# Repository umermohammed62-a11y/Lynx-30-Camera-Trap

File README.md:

Lynx-30: Simulation-Driven Low-Power Long-Range Camera Trap System

Overview

Lynx-30 is a low-power wireless camera trap system designed around the ESP32-CAM module. The system combines motion detection, infrared illumination, and efficient power management to provide battery-powered image capture for wildlife monitoring and remote sensing applications.

The project was developed using a modular hierarchical design approach and includes complete schematic capture, PCB layout, BOM generation, and manufacturing-ready Gerber files.

Features

* Low-power battery-powered operation
* ESP32-CAM image capture and wireless connectivity
* PIR-based motion detection
* Infrared illumination for night operation
* High-efficiency TPS63060 power architecture
* 5V and 3.3V regulated power rails
* PMOS-based power gating for IR LEDs
* Hierarchical schematic design
* Manufacturing-ready PCB design
* Support for 2-layer and 4-layer PCB stackups

System Architecture

Battery
   ↓
TPS63060 Buck-Boost Converter
   ↓
V_SYS_5V
   ├── ESP32-CAM
   ├── IR Illumination
   └── LDO Regulator
           ↓
        V_SYS_3V3
           ├── PIR Sensor
           └── Control Logic

Hardware Components

Main Controller

* ESP32-CAM AI Thinker Module

Power Management

* TPS63060 Buck-Boost Converter
* 3.3V LDO Regulator

Motion Detection

* PIR Sensor Module

Illumination

* IR LEDs
* PMOS High-Side Switching Circuit

Interfaces

* UART Programming Header
* MicroSD Storage

Power Architecture

The system uses a TPS63060 high-efficiency buck-boost converter to generate a regulated 5V rail from battery input.

The 5V rail supplies:

* ESP32-CAM
* IR illumination circuit

A secondary LDO regulator generates a 3.3V rail for:

* PIR sensor
* Control logic
* MOSFET gate drive circuitry

PCB Stackup

2-Layer Version

* Top Layer: Components and signal routing
* Bottom Layer: Ground plane

4-Layer Version

* Layer 1: Signal routing
* Layer 2: Ground plane
* Layer 3: Power plane
* Layer 4: Signal routing

Design Tools

* KiCad

Project Structure

Lynx-30-Camera-Trap
│
├── Documentation
│   ├── Project_Report.pdf
│   ├── System_Architecture.pdf
│   └── Design_Notes.pdf
│
├── KiCad
│   ├── Schematics
│   ├── PCB
│   └── Libraries
│
├── Gerbers
│
├── BOM
│   └── BOM.csv
│
├── Images
│   ├── PCB_Top.png
│   ├── PCB_Bottom.png
│   ├── PCB_3D.png
│   └── System_Block_Diagram.png
│
└── README.md
```
Deliverables

* Complete hierarchical schematic
* PCB layout
* BOM (Bill of Materials)
* Gerber files
* Pick-and-place files
* PCB 3D render images
* Engineering documentation

Future Improvements

* Deep sleep optimization
* Solar charging capability
* Machine learning-based object detection
* Cloud connectivity
* LoRa communication support
* Environmental sensors integration

Applications

* Wildlife monitoring
* Security surveillance
* Remote sensing
* Smart agriculture
* IoT edge devices

Author

Engr Umer Mohammed**

Electrical and Computer Engineer

Specialization: Power Engineering

Designed using professional PCB design practices with a focus on low-power embedded systems and manufacturable hardware.

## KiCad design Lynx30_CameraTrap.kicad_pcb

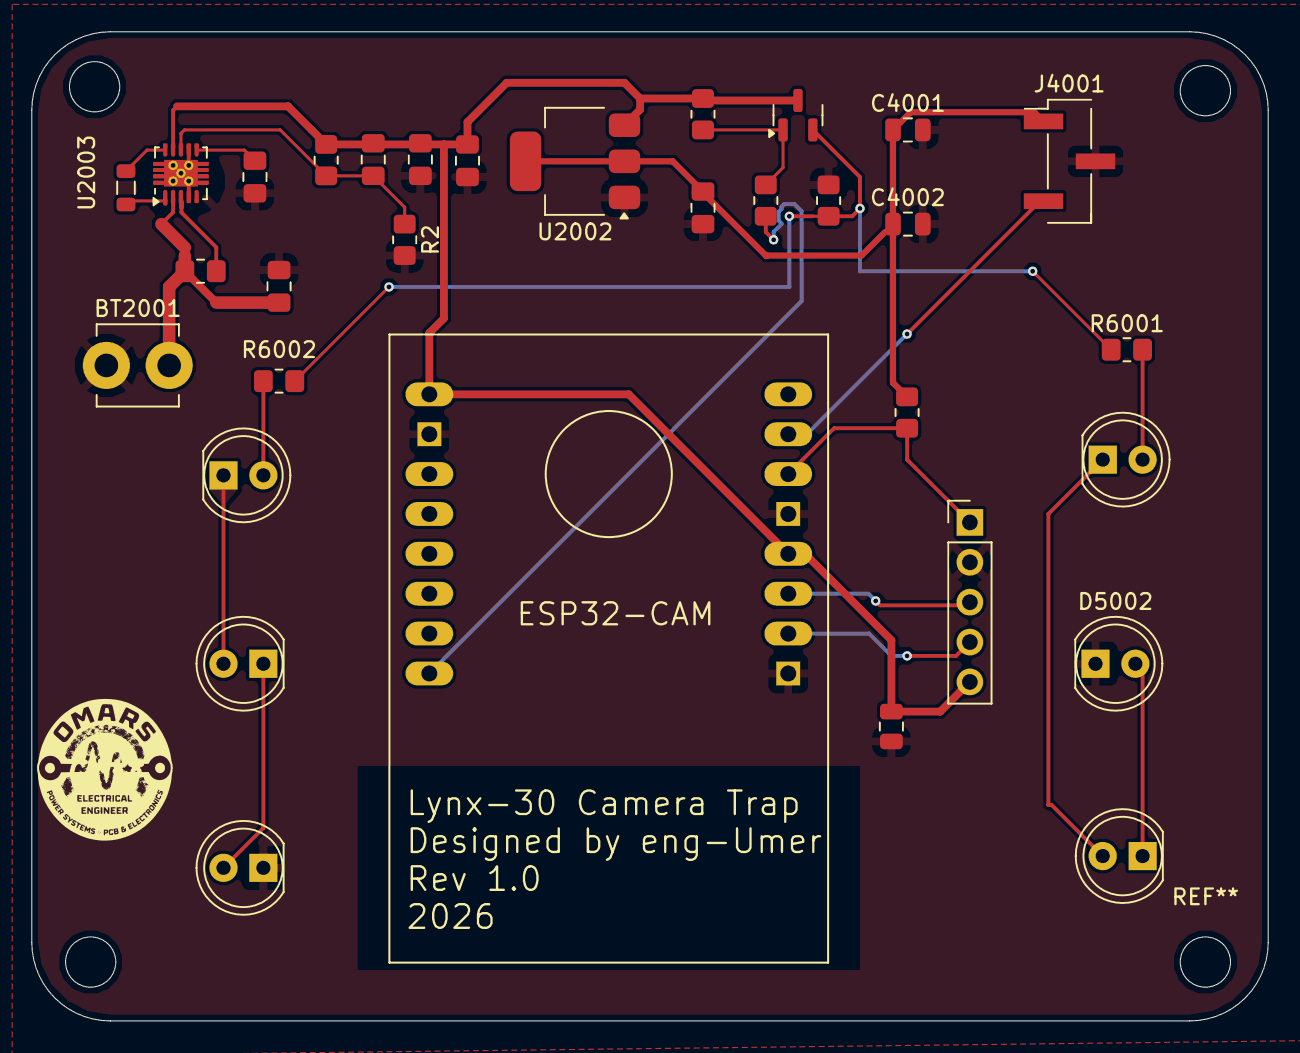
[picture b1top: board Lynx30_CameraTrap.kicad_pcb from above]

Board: 2 copper layers, 78.8 x 63.0 mm, 32 parts (0 on the bottom side), 22 nets.

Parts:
BT2001: Battery_Cell; TerminalBlock_MetzConnect_360410_1x01_Horizontal_ScrewM3.0
C2001: 10u; C_0805_2012Metric_Pad1.18x1.45mm_HandSolder
C2002: 10P; C_0805_2012Metric_Pad1.18x1.45mm_HandSolder
C2003: 47uF; C_0805_2012Metric_Pad1.18x1.45mm_HandSolder
C2004: 1U; C_0805_2012Metric_Pad1.18x1.45mm_HandSolder
C2005, C2006: 10uF; C_0805_2012Metric_Pad1.18x1.45mm_HandSolder
C3001, C4001: 0.1u; C_0805_2012Metric
C4002: 10u; C_0805_2012Metric
D5001, D5002, D5003, D5004, D6001, D6002: IRL81A; LED_D5.0mm
J3002: Conn_01x05_Pin; PinHeader_1x05_P2.54mm_Vertical
J4001: U_PIR_SENSOR; PinHeader_1x03_P2.54mm_Vertical_SMD_Pin1Left
L2001: 2.2uH; L_0805_2012Metric
Q2001: AO3401A; SOT-23
R1: 900K; R_0805_2012Metric_Pad1.20x1.40mm_HandSolder
R2, R3: 100K; R_0805_2012Metric_Pad1.20x1.40mm_HandSolder
R2002: 22n; R_0805_2012Metric_Pad1.20x1.40mm_HandSolder
R2004: 10k; R_0805_2012Metric_Pad1.20x1.40mm_HandSolder
R2005: 220n; R_0805_2012Metric_Pad1.20x1.40mm_HandSolder
R3001: R_US; R_0805_2012Metric_Pad1.20x1.40mm_HandSolder
R6001, R6002: 68; R_0805_2012Metric_Pad1.20x1.40mm_HandSolder
U2002: AMS1117-3.3; SOT-223-3_TabPin2
U2003: TPS63060; Texas_S-PWSON-N10_ThermalVias
U3001: ESP32-CAM

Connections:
/MCU_Control/IO0: J3002.1, R3001.1, U3001.P$6 (GPIO0)
/MCU_Control/RX: J3002.4, U3001.P$2 (GPIO1)
/MCU_Control/TX: J3002.3, U3001.P$3 (GPIO3)
GND: BT2001.1 (+), C2001.2, C2003.2, C2004.2, C2005.2, C2006.2, C3001.2, C4001.2, C4002.2, D5002.1 (K), D5003.1 (K), J3002.2, J4001.2, R2.2, R2002.2, U2002.1 (GND), U2003.4 (PS/SYNC), U2003.7 (GND), U2003.11 (PGND), U3001.P$1 (GND@1), U3001.P$5 (GND@2), U3001.P$10 (GND@3)
IR_PWR: Q2001.2 (S), R2002.1, R6001.1, R6002.1
MCU_IR_EN: R2005.2, U3001.P$16 (GPIO4)
unnamed: D5001.2 (A), D6001.1 (K)
unnamed: D5001.1 (K), D5002.2 (A)
unnamed: D5003.2 (A), D5004.1 (K)
unnamed: D5004.2 (A), D6002.1 (K)
unnamed: D6001.2 (A), R6001.2
unnamed: D6002.2 (A), R6002.2
unnamed: Q2001.1 (G), R2004.1, R2005.1
unnamed: R3.2, U2003.3 (EN)
unnamed: C2002.2, R1.2, R2.1, U2003.8 (FB)
unnamed: L2001.2, U2003.1 (L1)
unnamed: L2001.1, U2003.10 (L2)
unnamed: C2004.1, U2003.6 (VAUX)
PIR_SIGNAL: J4001.3, U3001.P$7 (GPIO16)
VBAT: BT2001.1 (+), C2001.1, R3.1, U2003.2 (VIN)
V_SYS_3V3: C2006.1, C4001.1, C4002.1, J4001.1, R3001.2, U2002.2 (VO)
V_SYS_5V: C2002.1, C2003.1, C2005.1, C3001.1, J3002.5, Q2001.3 (D), R1.1, R2004.2, U2002.3 (VI), U2003.9 (VOUT), U3001.P$4 (3V3/5V), U3001.P$9 (5V)

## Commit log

2026-06-12 Documentation/README.md
2026-06-12 Create Documentation
